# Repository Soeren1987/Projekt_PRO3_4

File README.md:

# Bruges til vores projekt uploading af koder og text filer

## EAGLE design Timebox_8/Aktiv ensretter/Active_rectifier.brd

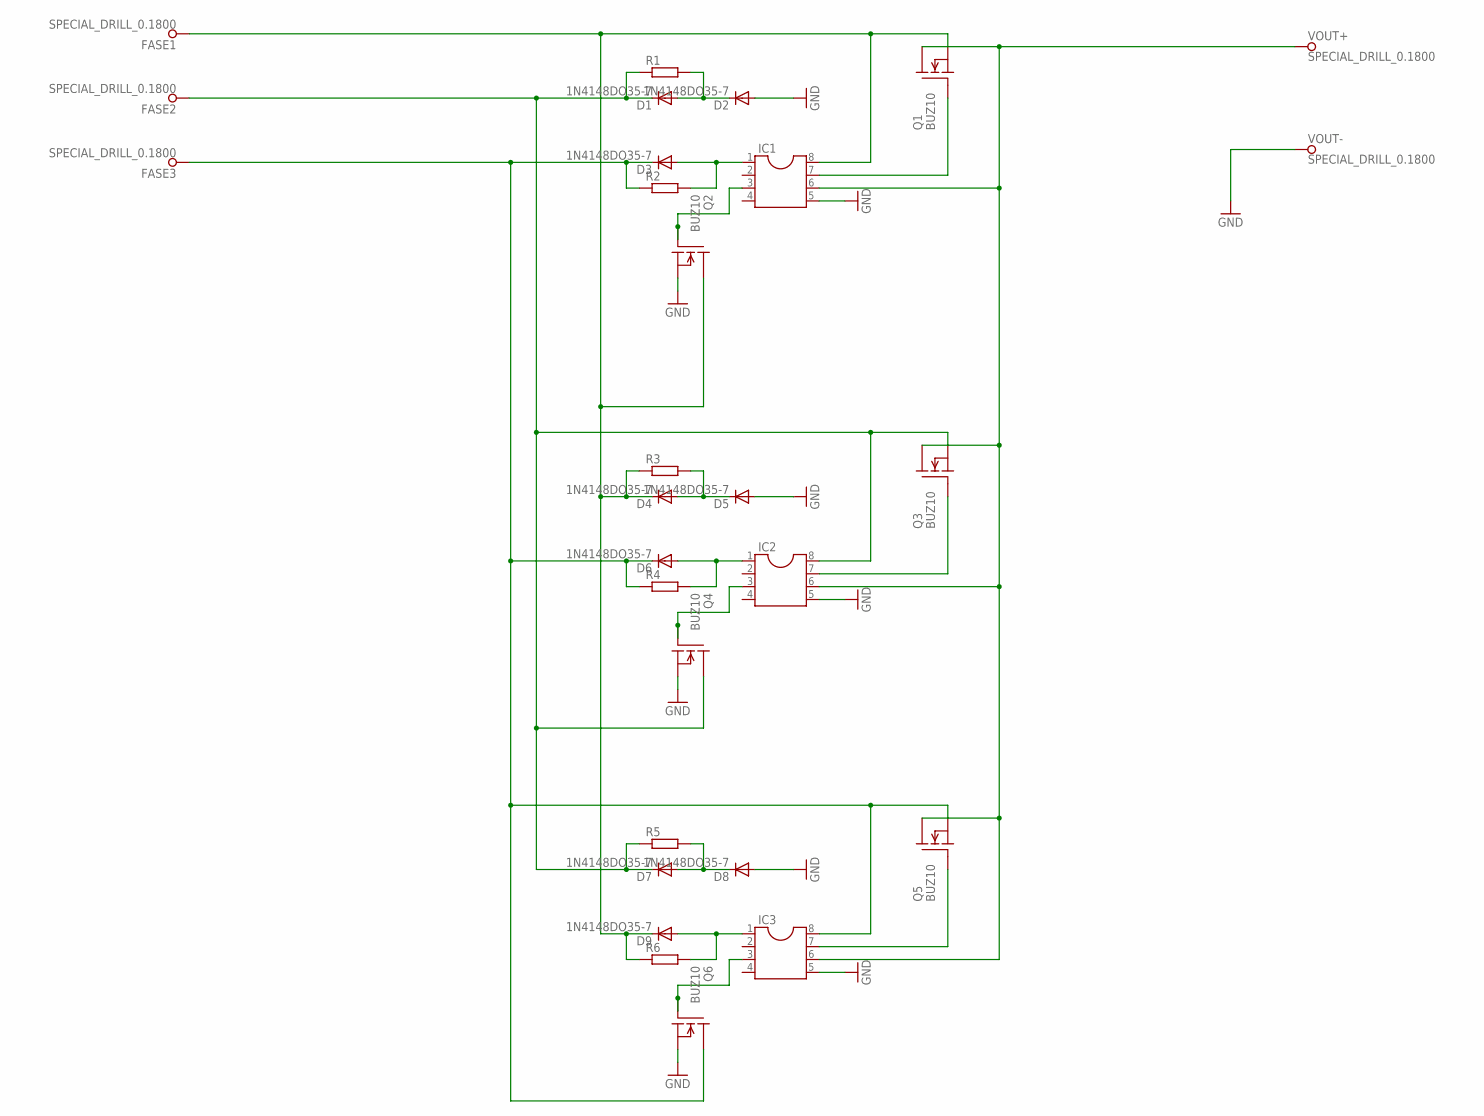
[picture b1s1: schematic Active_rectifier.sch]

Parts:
D1, D2, D3, D4, D5, D6, D7, D8, D9: 1N4148DO35-7; DO35-7
FASE1, FASE2, FASE3: SPECIAL_DRILL_0.1800; PAD_0.1800
IC1, IC2, IC3: DIL8; DIL08
Q1, Q2, Q3, Q4, Q5, Q6: BUZ10; TO220
R1, R2, R3, R4, R5, R6: R-EU_0207/10; 0207/10
VOUT+: SPECIAL_DRILL_0.1800; PAD_0.1800
VOUT-: SPECIAL_DRILL_0.1800; PAD_0.1800

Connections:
GND: D2.A, D5.A, D8.A, IC1.5, IC2.5, IC3.5, Q2.3 (S), Q4.3 (S), Q6.3 (S), VOUT-.1
unnamed: D1.A, D2.C, R1.2
unnamed: IC1.7, Q1.1 (G)
unnamed: D3.A, IC1.1, R2.2
unnamed: D4.A, D5.C, R3.2
unnamed: IC1.3, Q2.1 (G)
unnamed: D6.A, IC2.1, R4.2
unnamed: D3.C, D6.C, FASE3.1, IC3.8, Q5.3 (S), Q6.2 (D), R2.1, R4.1
unnamed: D7.A, D8.C, R5.2
unnamed: D4.C, D9.C, FASE1.1, IC1.8, Q1.3 (S), Q2.2 (D), R3.1, R6.1
unnamed: IC2.3, Q4.1 (G)
unnamed: D9.A, IC3.1, R6.2
unnamed: IC1.6, IC2.6, IC3.6, Q1.2 (D), Q3.2 (D), Q5.2 (D), VOUT+.1
unnamed: IC2.7, Q3.1 (G)
unnamed: D1.C, D7.C, FASE2.1, IC2.8, Q3.3 (S), Q4.2 (D), R1.1, R5.1
unnamed: IC3.3, Q6.1 (G)
unnamed: IC3.7, Q5.1 (G)

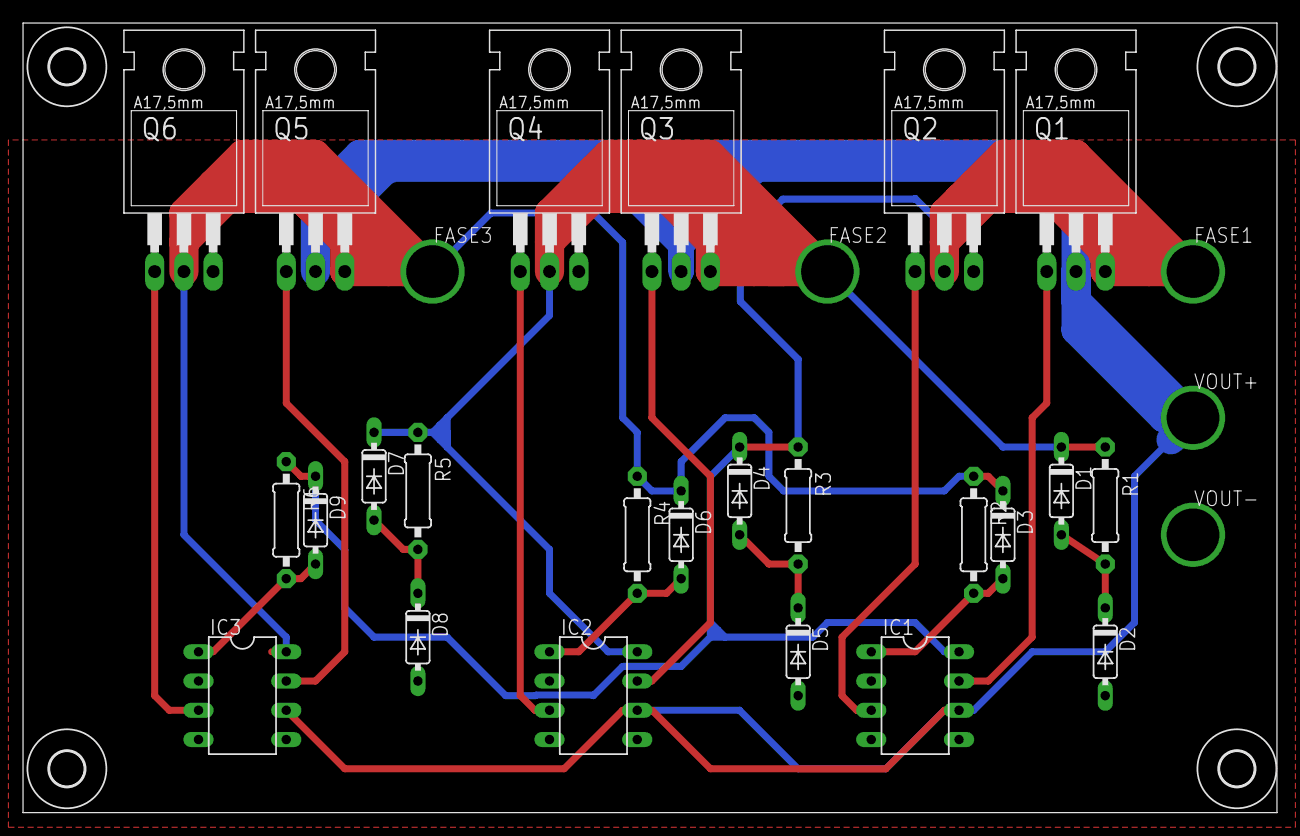
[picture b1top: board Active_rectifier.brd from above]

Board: 2 copper layers, 108.9 x 68.6 mm, 33 parts (0 on the bottom side), 17 nets.

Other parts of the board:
U$5, U$6, U$7, U$8: 3,0

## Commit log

2019-02-04 anden forsøg
2019-02-04 Endelig rettelse
2019-02-04 Servo driver ver 1.0
2019-02-07 ver 1.0 timebox 4
2019-02-07 ver 1.1 med billeder tilføjet
2019-02-08 ver 1.1 de endelige rettelser
2019-02-09 Kladde til Ensretter og spændingsregulator tilføjet - Timebox 4
2019-02-11 Opdeling i mapper
2019-02-11 Regler for timebox
2019-02-11 filer blevet slettet
2019-02-11 Test push/commit, Jonas
2019-02-11 test fil
2019-02-11 dette er en test fil
2019-02-12 Word doc med samlet timebox 4 og motorstyr.tex og motorstyr.pdf tilføjet
2019-02-12 Nu også med samlet word dokument
2019-02-12 og til sidst også motorstyr.txt
2019-02-13 Timebox 4 pdf vedlagt til rettelser mm. Png filer tilføjet (tilhører Sørens afsnit)
2019-02-13 PDF (Rettelser_til_TB4_TDJ) tilføjet til repo
2019-02-14 Tilføjet færdige timebox4 rapport
2019-02-18 Beskrivelse af testen af servo driver
2019-02-19 Tilføjet Klaus' kommentarer til timebox4
2019-02-19 Begrundelse for valg af regulator tilføjet til Spændingsregulator.docx
2019-02-19 Tilføjet v1.2 af tb-rapport
2019-02-19 opdateret tb4 ift. rettelse fra Thomas
2019-02-19 opdateret tb4 rapport
2019-02-27 beskrivelse af starter koden søren
2019-02-27 Analyse_Verifikation_Elstarter.docx tilføjet til mappen
2019-02-28 Tilføjet rapport for tb5 + figurer i png-format
2019-02-28 Uploadet endelig timebox5 rapport
2019-02-28 rettet filnavn
2019-03-05 Test af generator output tilføjet til timebox 6/TDJ
2019-03-06 timebox 6, pdf, kode senere
2019-03-06 nu med kode
2019-03-07 opdateret en fejl i ohm
2019-03-07 klar fra Simons side til aflevering i dag kl 12
2019-03-09 strategy and planning
2019-03-10 timebox 6 klar til deplyment
2019-03-10 done timebox6
2019-03-16 Rettelser til Test_generator_output tilføjet(Ny titel, nyt krav, blokdiagram mm)/TDJ
2019-03-17 tilrettet test af generator output
2019-03-17 tilretning af figurer
2019-03-27 Mappe Timebox_7 tilføjet repo. Billeder fra målinger af ensretter tilføjet
2019-03-28 måling af gate på ensretter
2019-03-29 Development Plan tilføjet
2019-03-29 Strategy and Planning til TB7 tilføjet
2019-03-29 Billeder + Design af teststand og simulering af ensretter tilføjet
2019-03-29 Realisering og målinger til timebox
2019-03-29 tilføjet motorstyring til dev plan
2019-04-01 timebox7 færdig
2019-04-05 CSV data fra målinger af stepinput tilføjet TB8 - OBS!!!!!! 3. måling er bedst
2019-04-09 nye målinger af til steprespons 9/4 (1_moling.csv og 2_moling.csv)
2019-04-09 nye målinger af til steprespons 9/4 (1_moling.csv)
2019-04-09 OBS!!!! data_1 og data_2 er de rigtige målinger. 9/4
2019-04-10 Eagle filer til PCB til aktiv ensretter tilføjet. TB8
2019-04-25 Word doc med beskrivelse af PCB design samt billeder af print tilføjet
2019-04-25 Lille ændring til PCB.docx lavet
2019-04-25 .sch og .brd filer ændret
2019-04-26 .Ændring af PCB.docx - nu med loddet print
2019-04-29 kode til at aflæse rpm, mangler at blive testet
2019-05-01 Timebox 8 rapport færdig til gennemsyn
2019-05-03 beskrivelse af RPM koden
2019-05-05 Funktionalitetstest af ensretter oprettet og tilføjet TB9
2019-05-05 Funktionalitetstest af ensretter tilrettet
2019-05-05 Jacobs word-doc tilføjet
2019-05-05 vin_vs_vout.m ændret
2019-05-05 Lidt Gramma ændringer til min del :-)
2019-05-05 timebox klar
2019-05-06 koden fra RPM dokument
2019-05-06 RPM kode fra dokument
2019-05-09 deployment tilført
2019-05-10 Add files via upload
    TIlføjelse til TB8
2019-05-13 opdateret T9
2019-05-15 projektmappe med pid-kode
2019-05-16 jeg har tilføjet rpm-detect, omdøbt til .cpp og rettet i main, sådan at init_read_rpm() falder udenfor main og FreeRTOS er deaktiveret.
2019-05-24 Mappe til den den endelig rapport, hvori der en mappe med alle timebox PDF'er samlet
2019-05-24 Her er min del til rapporten. Søren
2019-05-24 Udkast til afsnit om ensretter tilføjet. Er dog ikke færdig endnu.
2019-05-25 motorstyring tilføjet
2019-05-26 struktur for rapport
2019-05-27 Afsnit til ensretter nu som zip
2019-05-27 Add files via upload
    Introduktion opdateret
2019-05-27 Proces beskrivelsen til rapporten
2019-05-27 opdatering af proces beskrivelse
2019-05-27 hovedrengøring af rapportmappe
2019-05-27 tilfÃ¸jelse af ensretter
2019-05-27 materiale i rapport
2019-05-27 gennemgang af rapportindhold
2019-05-28 report layout done
2019-05-28 tilfÃ¸jelser til rapport
2019-05-28 Endelig rapport med rettelser/tilføjelser af Thomas
2019-05-28 opdateret rapport
2019-05-28 mangler konklusion
2019-05-28 opdatering af forside
2019-05-28 opdatering af indholdsfortegnelse
2019-05-29 Nye rettelser til seneste rapport pdf - TDJ
2019-05-29 fÃ¦rdig rapport
2019-05-29 tb10
2019-05-29 til aflevering
2019-06-12 Fælles PP slide tilføjet.
